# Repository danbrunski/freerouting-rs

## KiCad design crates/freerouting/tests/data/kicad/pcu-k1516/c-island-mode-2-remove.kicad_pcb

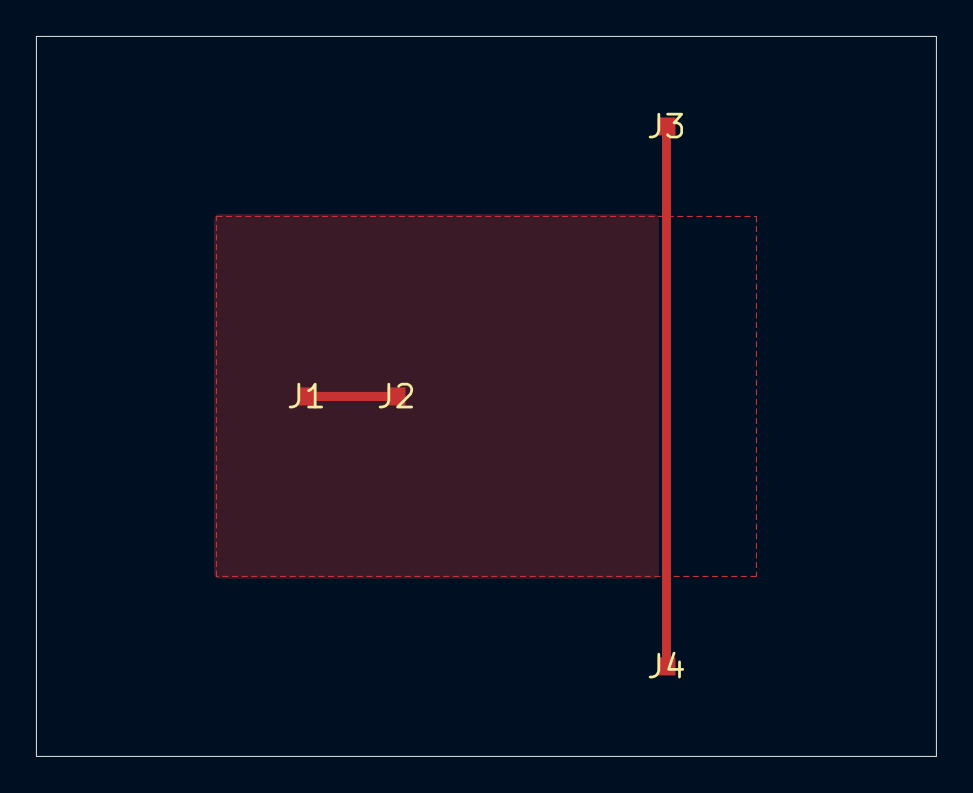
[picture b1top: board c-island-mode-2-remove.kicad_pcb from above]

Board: 4 copper layers, 50.0 x 40.0 mm, 4 parts (0 on the bottom side), 2 nets.

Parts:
J1, J2, J3, J4: x; smd

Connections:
N1: J1.1, J2.1
N2: J3.1, J4.1
